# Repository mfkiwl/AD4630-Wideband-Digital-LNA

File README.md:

# AD4630 Wideband Digital LNA
## Introduction
Output noise is an important metric when it comes to evaluating the performance of precision voltage references (temperature coefficient and stability being others). Of particular interest is the frequency band between 0.1Hz and 10Hz. Most long-scale integrating ADCs feature measurement periods that lie in this band, so the internal reference should ideally have noise lower than measurement resolution over this time period. To measure noise in this band, an amplifier, itself having low noise, is needed. Appropriate filtering is also desired to keep out excess noise (of other frequencies) from contaminating the band of interest. 
## Project Motivation
This idea was originally proposed to me by [Marco Reps](https://www.youtube.com/@reps), which was in turn based on an idea [Mark](https://github.com/macaba) had told him about - a digital sampler that would send raw samples to a computer program that would filter to the required bandwidth digitally. Given the 2Msps sample rate of the AD4630, the upper frequency limit could be expanded to several kilohertz. The addition of a chopper preamp would also greatly reduce input noise. DC-coupling the input and adding a few preamps in parallel would also make a crude nanovoltmeter. This project is intended mainly to explore the AD4630 itself, and evaluate possible front end circuits.
### Goals:
- Wideband sampling and digitally filtering samples to desired bandwidth
- Ultralow 1/f corner front end with AC and DC paths for noise and nanovolt measurements (TBD)
- Optically isolated digital and analog sections: This is achieved easiest using a separate controller for front-end side, and using something like a UART isolator and a UART-USB bridge on the other side. 
- Battery powered (front end at least, digital section USB powered): This one might be a bit challenging, for example, what kind of batteries will be used? What voltages to power the front end with? Single ended or bipolar?
### Challenges: 
- Evaluating noise performance
- Implementing optical isolation and battery power
## Usage
### Specifications:
- 10mHz to 10kHz input bandwidth    [calculated]
- x200000 (106dB)                   [calculated]
- ~3.5nV/rtHz noise floor (full BW) [calculated]
## List of Files
- Hardware: KiCAD PCB files.

- Software: [under construction]
  - Simulation: LTspice .asc file.
- Resources: Infographics.
## Application Examples
[under construction]
- The LNA outputs raw samples that can be stored in a .csv file and interpreted by an [NSD](https://github.com/macaba/NSD) program. 
## Notes
- The AD4630 is pin-compatible with the AD4030, which opens up some interesting possibilities in the future.
- The input stage consists of a Sallen-Key filter that filters out frequencies below 10mHz while providing a gain of 330. It is possible to have gain and filtering in the same stage because of the low Thevenin resistance of the amplifier feedback resistors. The input filter/gain stage is followed by another x330 gain stage, which in turn is followed by a fully-differential amplifier (x2) to convert the input swing to a differential swing for the ADC. It should theoretically be possible to cancel reference noise by setting fully differential amplifier common mode voltage to 1/2\*Vref as well as referencing one of the ADC differential inputs to 1/2\*Vref. Overall gain is 200000.

## Links
- https://www.analog.com/media/en/technical-documentation/data-sheets/ad4630-24_ad4632-24.pdf
- https://www.analog.com/media/en/technical-documentation/data-sheets/ada4528-1_4528-2.pdf
- https://www.analog.com/media/en/technical-documentation/data-sheets/6362fa.pdf
- http://sim.okawa-denshi.jp/en/OPseikiHikeisan.htm
- http://www.dicks-website.eu/low_noise_amp_part1/part1.html

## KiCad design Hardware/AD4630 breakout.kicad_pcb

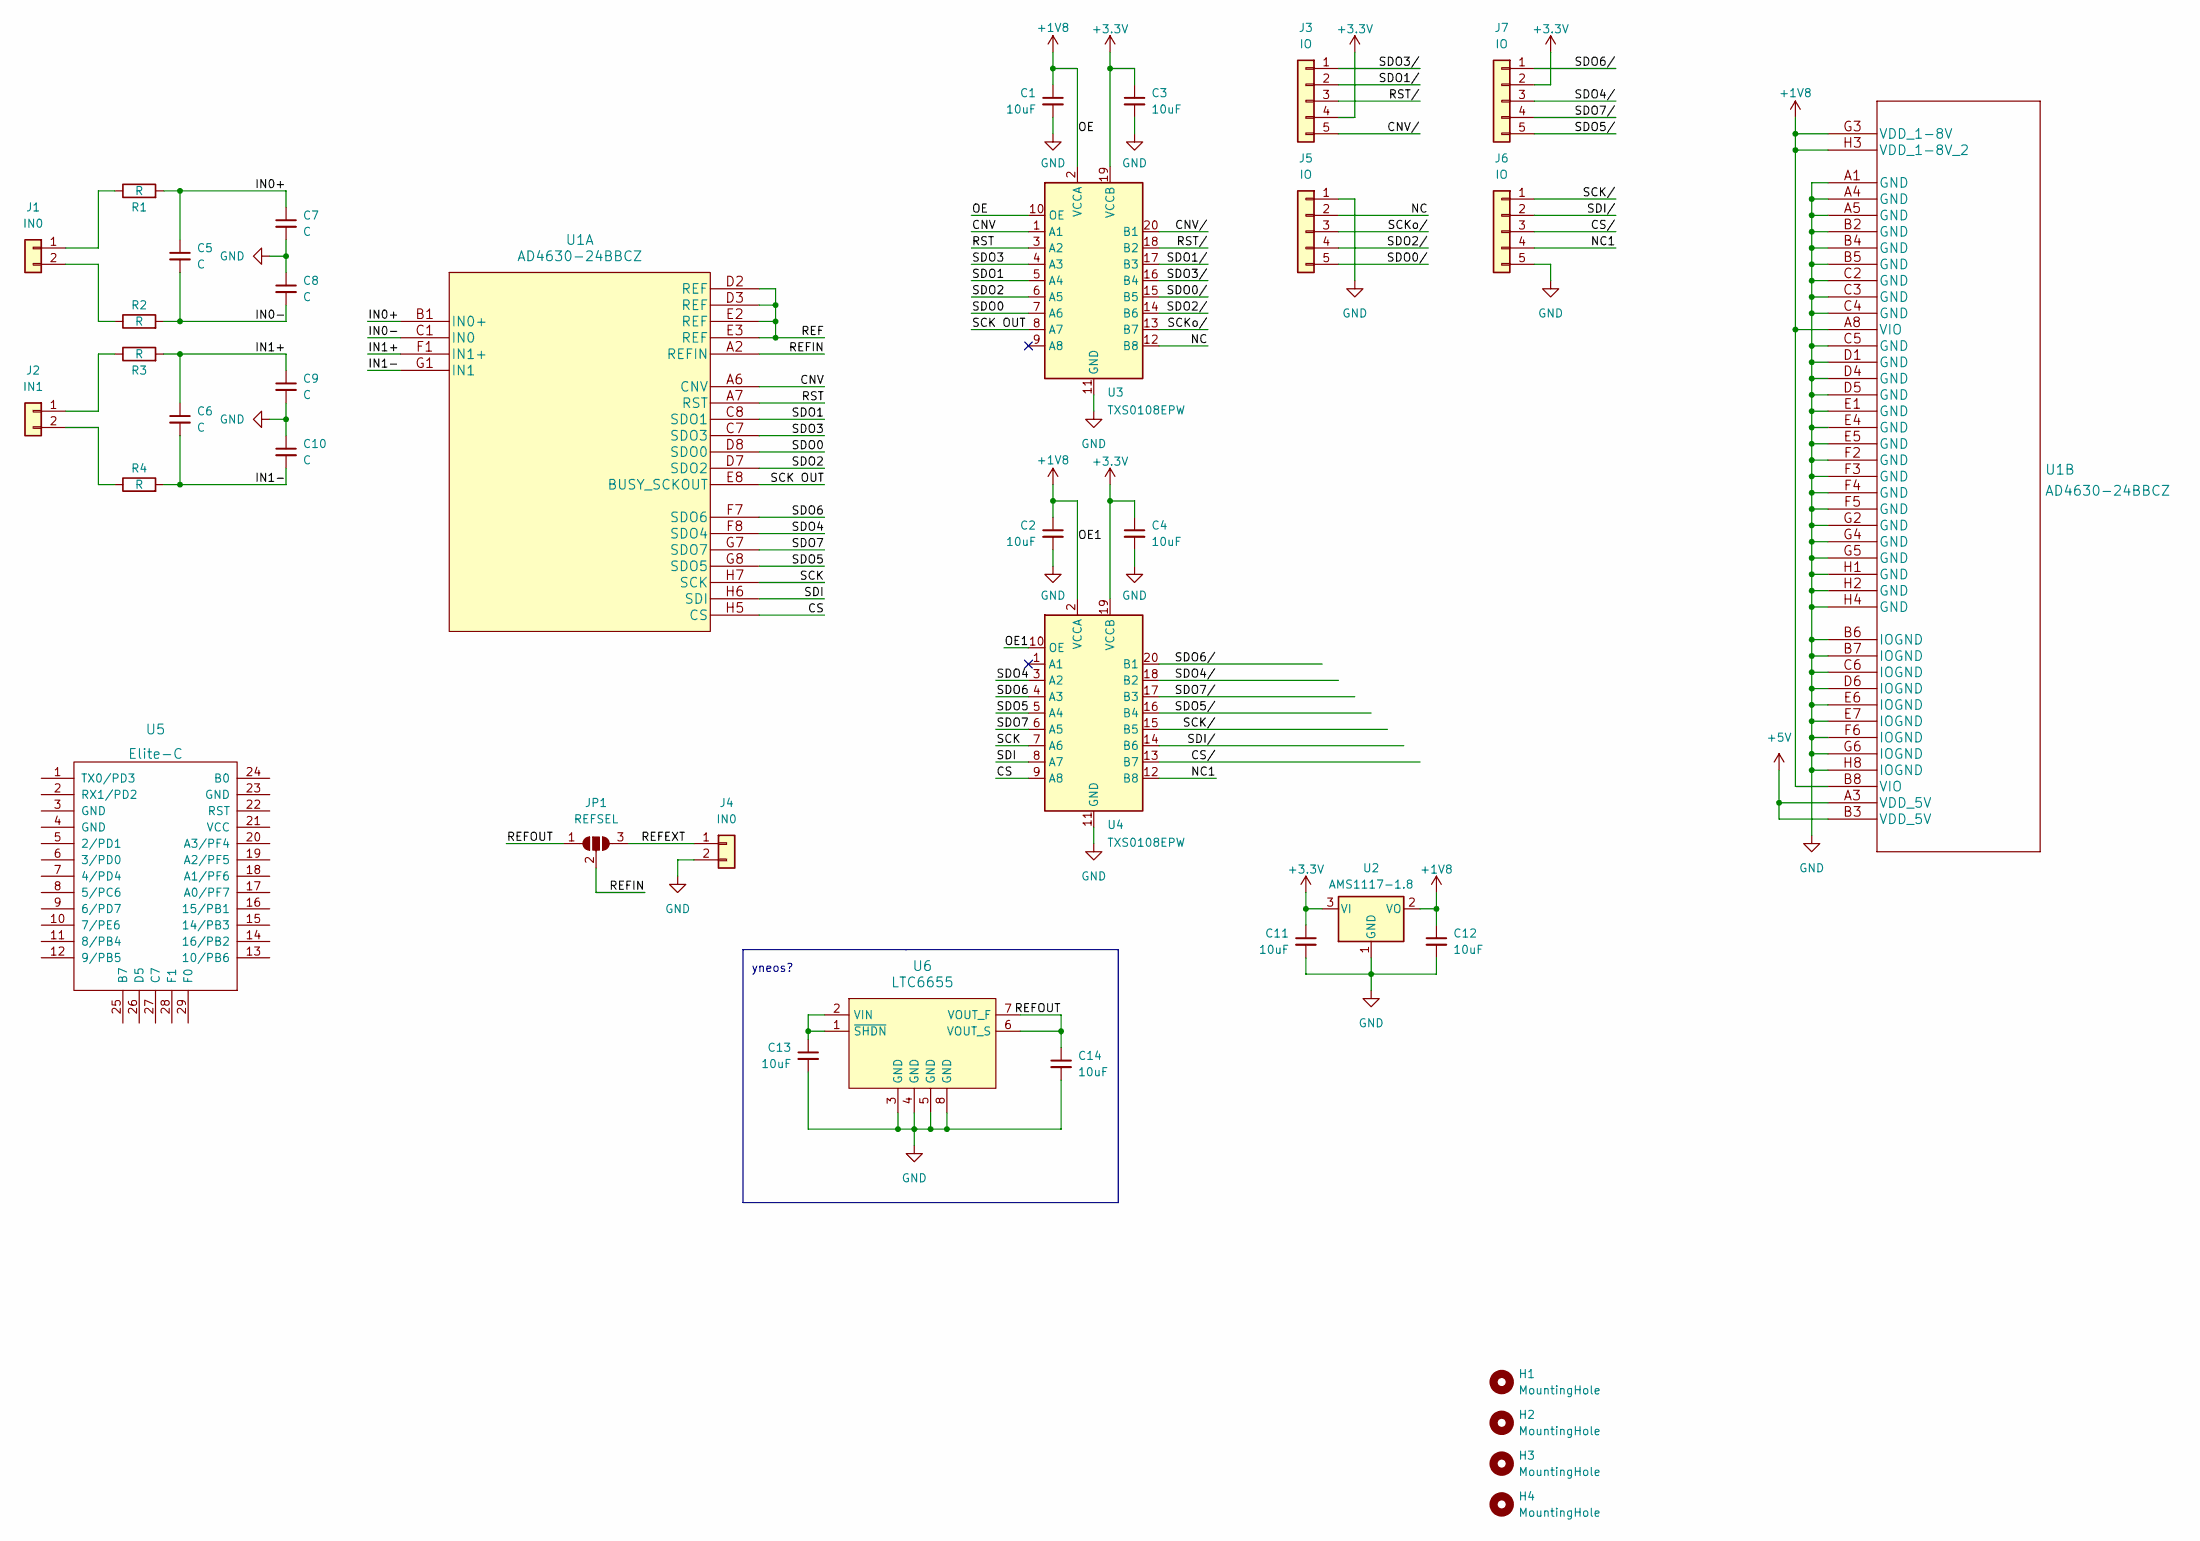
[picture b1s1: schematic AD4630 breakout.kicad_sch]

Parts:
C1, C2, C3, C4, C11, C12, C13, C14: 10uF; C_0603_1608Metric
C5, C6, C7, C8, C9, C10: C; C_0603_1608Metric
H1, H2, H3, H4: MountingHole; MountingHole_3.2mm_M3_Pad_Via
J1, J4: IN0; PinHeader_1x02_P2.00mm_Vertical
J2: IN1; PinHeader_1x02_P2.00mm_Vertical
J3, J5, J6, J7: IO; PinHeader_1x05_P2.00mm_Vertical
JP1: REFSEL; SolderJumper-3_P1.3mm_Open_RoundedPad1.0x1.5mm
R1, R2, R3, R4: R; R_0603_1608Metric
U1: AD4630-24BBCZ
U2: AMS1117-1.8; SOT-89-3
U3, U4: TXS0108EPW; TSSOP-20_4.4x6.5mm_P0.65mm
U5: Elite-C; Elite-C-castellated-29pin-holes
U6: LTC6655; LTC6655BHLS8-5-PBF

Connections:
+1V8: C1.1, C2.1, C12.1, U1.A8 (VIO), U1.B8 (VIO), U1.G3 (VDD_1-8V), U1.H3 (VDD_1-8V_2), U2.2 (VO), U3.2 (VCCA), U3.10 (OE), U4.2 (VCCA), U4.10 (OE)
+3V3: C3.1, C4.1, C11.1, J3.4, J7.2, U2.3 (VI), U3.19 (VCCB), U4.19 (VCCB)
+5V: U1.A3 (VDD_5V), U1.B3 (VDD_5V)
/CNV: U1.A6 (CNV), U3.1 (A1)
/CNV/: J3.5, U3.20 (B1)
/CS: U1.H5 (CS), U4.9 (A8)
/CS/: J6.3, U4.13 (B7)
/IN0+: C5.1, C7.1, R1.2, U1.B1 (IN0+)
/IN0-: C5.2, C8.2, R2.2, U1.C1 (IN0)
/IN1+: C6.1, C9.1, R3.2, U1.F1 (IN1+)
/IN1-: C6.2, C10.2, R4.2, U1.G1 (IN1)
/NC: J5.2, U3.12 (B8)
/NC1: J6.4, U4.12 (B8)
/REF: U1.D2 (REF), U1.D3 (REF), U1.E2 (REF), U1.E3 (REF)
/REFEXT: J4.1, JP1.3 (B)
/REFIN: JP1.2 (C), U1.A2 (REFIN)
/REFOUT: C14.1, JP1.1 (A), U6.6 (VOUT_S), U6.7 (VOUT_F)
/RST: U1.A7 (RST), U3.3 (A2)
/RST/: J3.3, U3.18 (B2)
/SCK: U1.H7 (SCK), U4.7 (A6)
/SCK OUT: U1.E8 (BUSY_SCKOUT), U3.8 (A7)
/SCKo/: J5.3, U3.13 (B7)
/SCK/: J6.1, U4.15 (B5)
/SDI: U1.H6 (SDI), U4.8 (A7)
/SDI/: J6.2, U4.14 (B6)
/SDO0: U1.D8 (SDO0), U3.7 (A6)
/SDO0/: J5.5, U3.15 (B5)
/SDO1: U1.C8 (SDO1), U3.5 (A4)
/SDO1/: J3.2, U3.17 (B3)
/SDO2: U1.D7 (SDO2), U3.6 (A5)
/SDO2/: J5.4, U3.14 (B6)
/SDO3: U1.C7 (SDO3), U3.4 (A3)
/SDO3/: J3.1, U3.16 (B4)
/SDO4: U1.F8 (SDO4), U4.3 (A2)
/SDO4/: J7.3, U4.18 (B2)
/SDO5: U1.G8 (SDO5), U4.5 (A4)
/SDO5/: J7.5, U4.16 (B4)
/SDO6: U1.F7 (SDO6), U4.4 (A3)
/SDO6/: J7.1, U4.20 (B1)
/SDO7: U1.G7 (SDO7), U4.6 (A5)
/SDO7/: J7.4, U4.17 (B3)
GND: C1.2, C2.2, C3.2, C4.2, C7.2, C8.1, C9.2, C10.1, C11.2, C12.2, C13.2, C14.2, J4.2, J5.1, J6.5, U1.A1 (GND), U1.A4 (GND), U1.A5 (GND), U1.B2 (GND), U1.B4 (GND), U1.B5 (GND), U1.B6 (IOGND), U1.B7 (IOGND), U1.C2 (GND), U1.C3 (GND), U1.C4 (GND), U1.C5 (GND), U1.C6 (IOGND), U1.D1 (GND), U1.D4 (GND), U1.D5 (GND), U1.D6 (IOGND), U1.E1 (GND), U1.E4 (GND), U1.E5 (GND), U1.E6 (IOGND), U1.E7 (IOGND), U1.F2 (GND), U1.F3 (GND), U1.F4 (GND), U1.F5 (GND), U1.F6 (IOGND), U1.G2 (GND), U1.G4 (GND), U1.G5 (GND), U1.G6 (IOGND), U1.H1 (GND), U1.H2 (GND), U1.H4 (GND), U1.H8 (IOGND), U2.1 (GND), U3.11 (GND), U4.11 (GND), U6.3 (GND), U6.4 (GND), U6.5 (GND), U6.8 (GND)
unnamed: C13.1, U6.1 (~SHDN), U6.2 (VIN)
unnamed: J1.1, R1.1
unnamed: J1.2, R2.1
unnamed: J2.1, R3.1
unnamed: J2.2, R4.1

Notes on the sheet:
yneos?

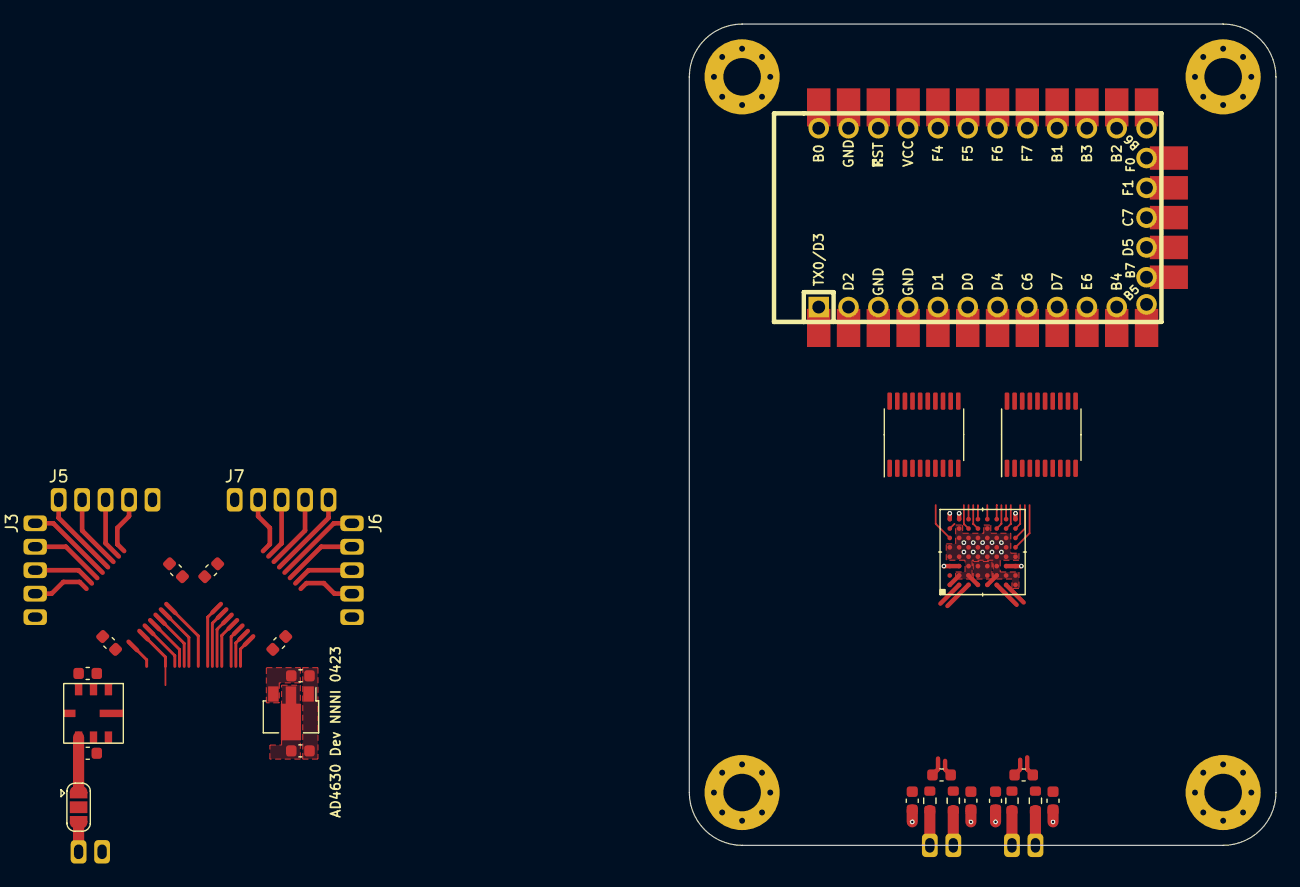
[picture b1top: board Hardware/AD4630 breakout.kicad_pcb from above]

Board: 4 copper layers, 50.0 x 70.0 mm, 36 parts (0 on the bottom side), 47 nets.

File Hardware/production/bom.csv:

Designator,Footprint,Quantity,Value,LCSC Part #
"C1, C11, C12, C13, C14, C2, C3, C4",C_0603_1608Metric,8,10uF,
"C10, C5, C6, C7, C8, C9",C_0603_1608Metric,6,C,
"J1, J4",PinHeader_1x02_P2.54mm_Vertical,2,IN0,
J2,PinHeader_1x02_P2.54mm_Vertical,1,IN1,
"J3, J5, J6, J7",PinHeader_1x05_P2.00mm_Vertical,4,IO,
"R1, R2, R3, R4",R_0603_1608Metric,4,R,
U1,AD4630-24BBCZ,1,AD4630-24BBCZ,
U2,SOT-89-3,1,AMS1117-1.8,
"U3, U4",TSSOP-20_4.4x6.5mm_P0.65mm,2,TXS0108EPW,
U6,LTC6655BHLS8-5-PBF,1,LTC6655,

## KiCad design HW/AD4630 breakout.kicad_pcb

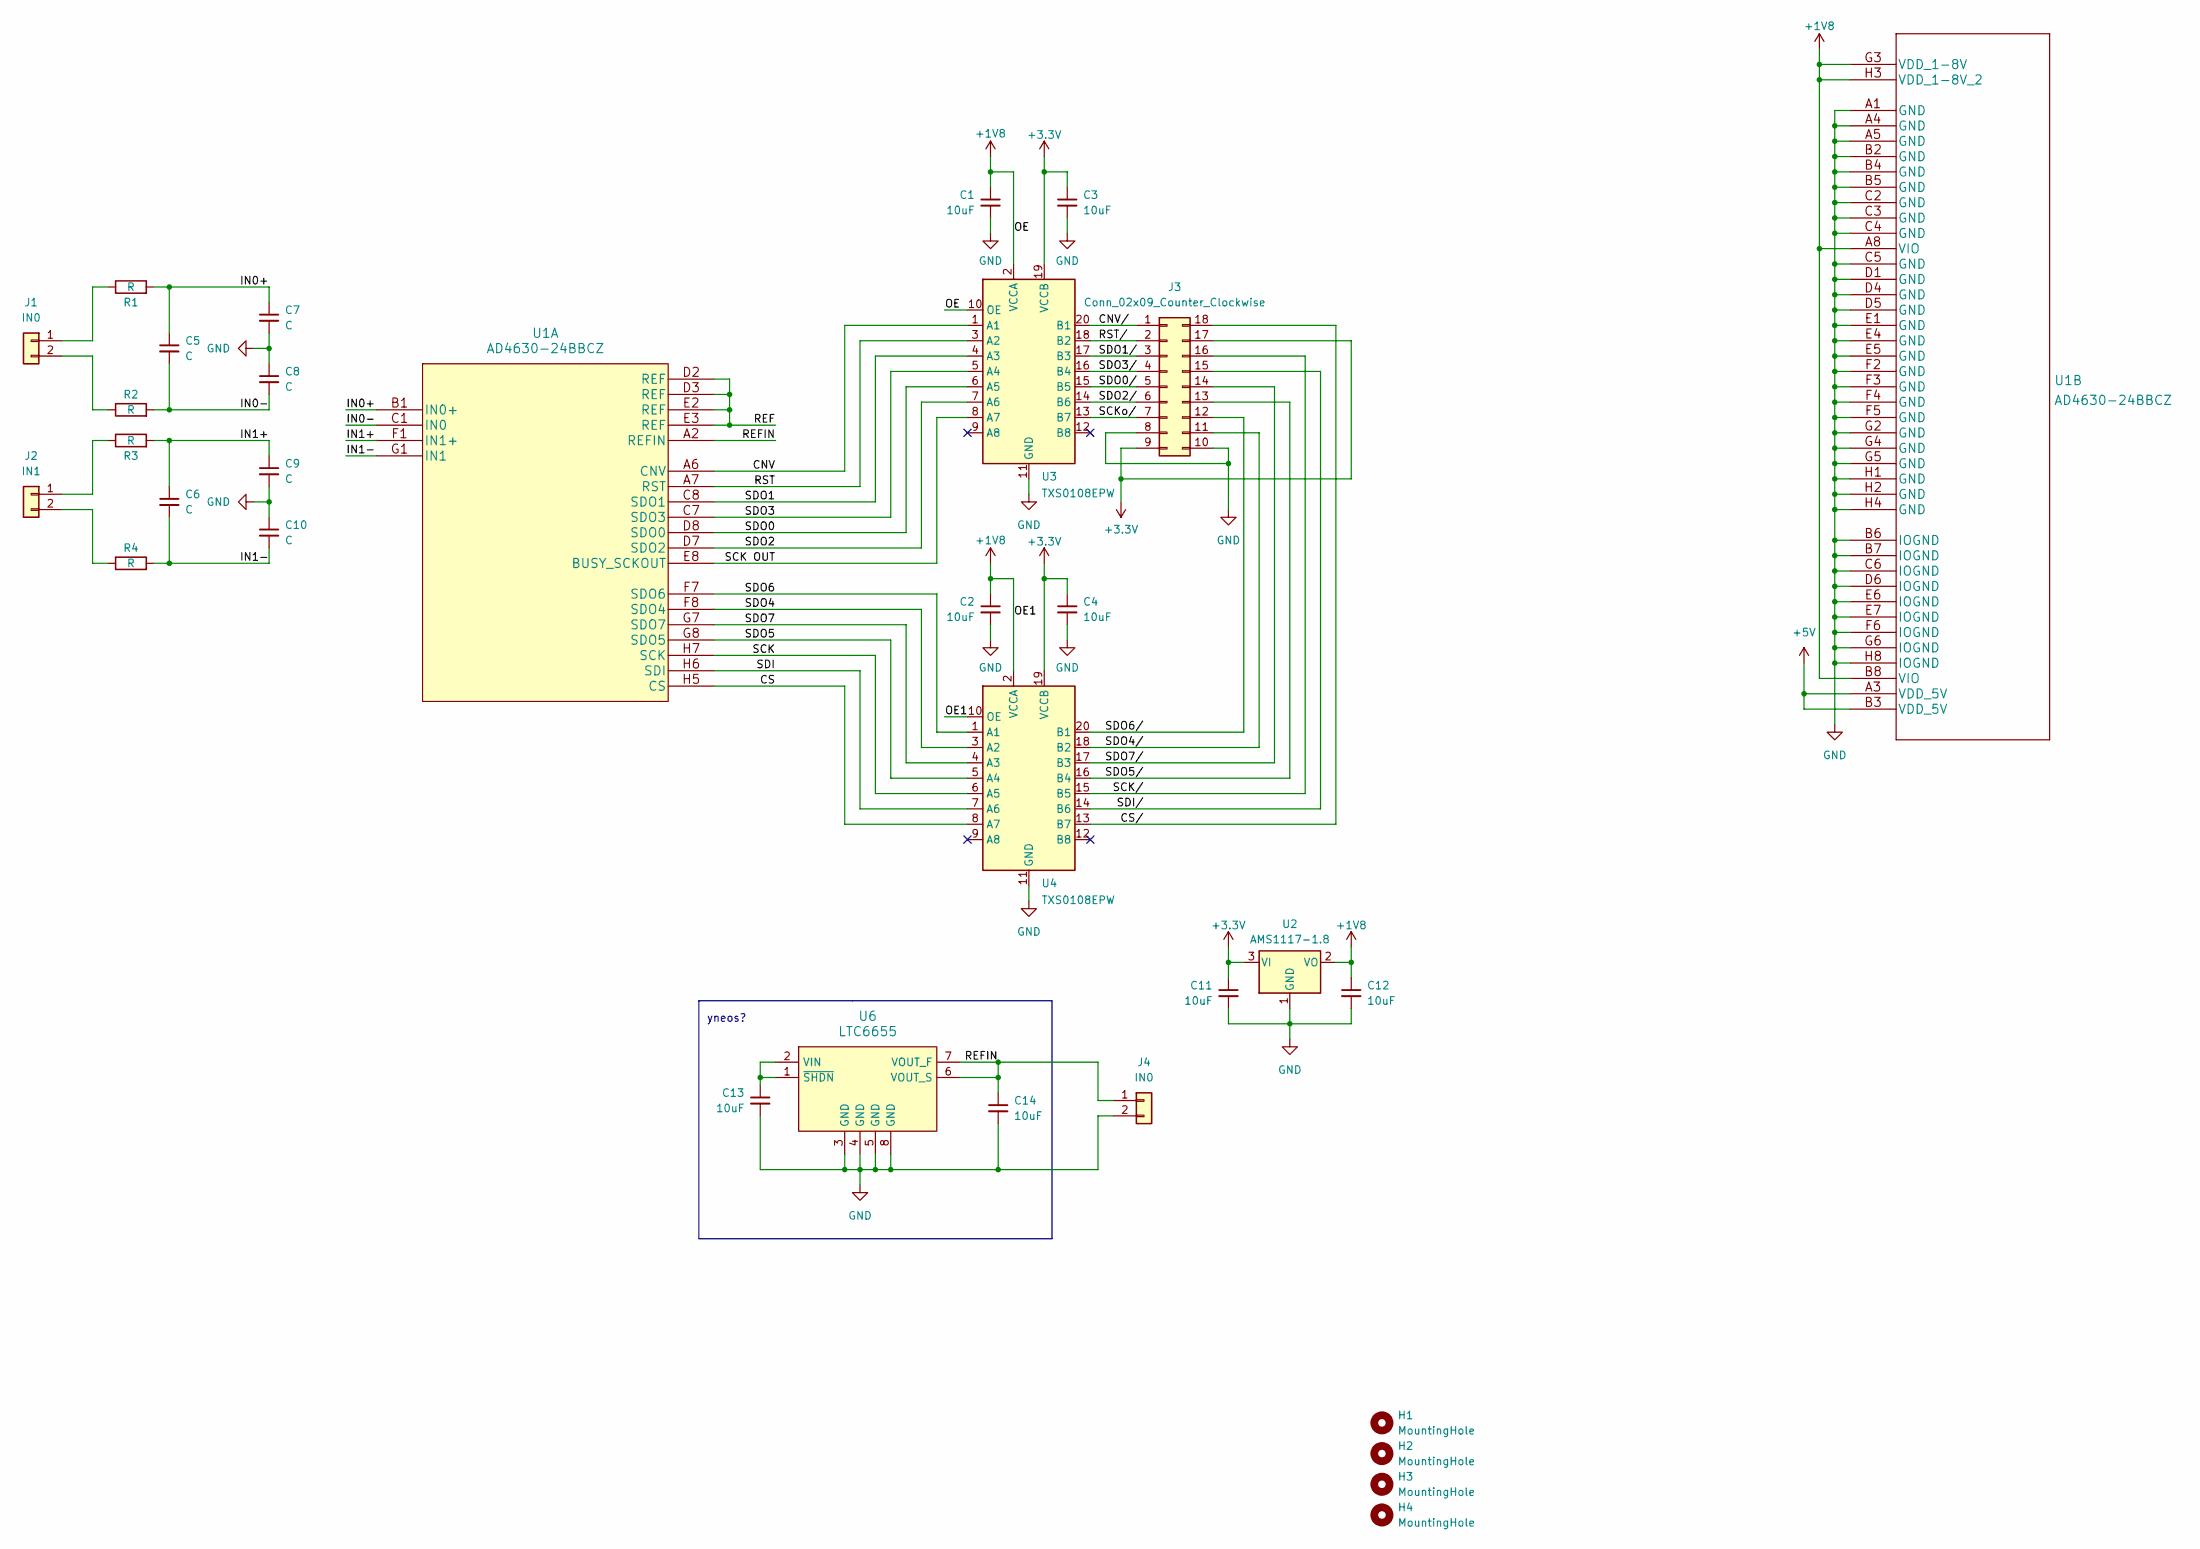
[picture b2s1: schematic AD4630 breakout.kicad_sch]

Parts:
C1, C2, C3, C4, C11, C12, C13, C14: 10uF; C_0603_1608Metric
C5, C6, C7, C8, C9, C10: C; C_0603_1608Metric
H1, H2, H3, H4: MountingHole; MountingHole_3.2mm_M3_Pad_Via
J1, J4: IN0; PinHeader_1x02_P2.54mm_Vertical
J2: IN1; PinHeader_1x02_P2.54mm_Vertical
J3: Conn_02x09_Counter_Clockwise; PinHeader_2x09_P2.54mm_Vertical
R1, R2, R3, R4: R; R_0603_1608Metric
U1: AD4630-24BBCZ
U2: AMS1117-1.8; SOT-89-3
U3, U4: TXS0108EPW; TSSOP-20_4.4x6.5mm_P0.65mm
U6: LTC6655; LTC6655BHLS8-5-PBF

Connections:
+1V8: C1.1, C2.1, C12.1, U1.A8 (VIO), U1.B8 (VIO), U1.G3 (VDD_1-8V), U1.H3 (VDD_1-8V_2), U2.2 (VO), U3.2 (VCCA), U3.10 (OE), U4.2 (VCCA), U4.10 (OE)
+3V3: C3.1, C4.1, C11.1, J3.9, J3.17, U2.3 (VI), U3.19 (VCCB), U4.19 (VCCB)
+5V: U1.A3 (VDD_5V), U1.B3 (VDD_5V)
/CNV: U1.A6 (CNV), U3.1 (A1)
/CNV/: J3.1, U3.20 (B1)
/CS: U1.H5 (CS), U4.8 (A7)
/CS/: J3.18, U4.13 (B7)
/IN0+: C5.1, C7.1, R1.2, U1.B1 (IN0+)
/IN0-: C5.2, C8.2, R2.2, U1.C1 (IN0)
/IN1+: C6.1, C9.1, R3.2, U1.F1 (IN1+)
/IN1-: C6.2, C10.2, R4.2, U1.G1 (IN1)
/REF: U1.D2 (REF), U1.D3 (REF), U1.E2 (REF), U1.E3 (REF)
/REFIN: C14.1, J4.1, U1.A2 (REFIN), U6.6 (VOUT_S), U6.7 (VOUT_F)
/RST: U1.A7 (RST), U3.3 (A2)
/RST/: J3.2, U3.18 (B2)
/SCK: U1.H7 (SCK), U4.6 (A5)
/SCK OUT: U1.E8 (BUSY_SCKOUT), U3.8 (A7)
/SCKo/: J3.7, U3.13 (B7)
/SCK/: J3.16, U4.15 (B5)
/SDI: U1.H6 (SDI), U4.7 (A6)
/SDI/: J3.15, U4.14 (B6)
/SDO0: U1.D8 (SDO0), U3.6 (A5)
/SDO0/: J3.5, U3.15 (B5)
/SDO1: U1.C8 (SDO1), U3.4 (A3)
/SDO1/: J3.3, U3.17 (B3)
/SDO2: U1.D7 (SDO2), U3.7 (A6)
/SDO2/: J3.6, U3.14 (B6)
/SDO3: U1.C7 (SDO3), U3.5 (A4)
/SDO3/: J3.4, U3.16 (B4)
/SDO4: U1.F8 (SDO4), U4.3 (A2)
/SDO4/: J3.11, U4.18 (B2)
/SDO5: U1.G8 (SDO5), U4.5 (A4)
/SDO5/: J3.13, U4.16 (B4)
/SDO6: U1.F7 (SDO6), U4.1 (A1)
/SDO6/: J3.12, U4.20 (B1)
/SDO7: U1.G7 (SDO7), U4.4 (A3)
/SDO7/: J3.14, U4.17 (B3)
GND: C1.2, C2.2, C3.2, C4.2, C7.2, C8.1, C9.2, C10.1, C11.2, C12.2, C13.2, C14.2, J3.8, J3.10, J4.2, U1.A1 (GND), U1.A4 (GND), U1.A5 (GND), U1.B2 (GND), U1.B4 (GND), U1.B5 (GND), U1.B6 (IOGND), U1.B7 (IOGND), U1.C2 (GND), U1.C3 (GND), U1.C4 (GND), U1.C5 (GND), U1.C6 (IOGND), U1.D1 (GND), U1.D4 (GND), U1.D5 (GND), U1.D6 (IOGND), U1.E1 (GND), U1.E4 (GND), U1.E5 (GND), U1.E6 (IOGND), U1.E7 (IOGND), U1.F2 (GND), U1.F3 (GND), U1.F4 (GND), U1.F5 (GND), U1.F6 (IOGND), U1.G2 (GND), U1.G4 (GND), U1.G5 (GND), U1.G6 (IOGND), U1.H1 (GND), U1.H2 (GND), U1.H4 (GND), U1.H8 (IOGND), U2.1 (GND), U3.11 (GND), U4.11 (GND), U6.3 (GND), U6.4 (GND), U6.5 (GND), U6.8 (GND)
unnamed: C13.1, U6.1 (~SHDN), U6.2 (VIN)
unnamed: J1.1, R1.1
unnamed: J1.2, R2.1
unnamed: J2.1, R3.1
unnamed: J2.2, R4.1

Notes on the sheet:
yneos?

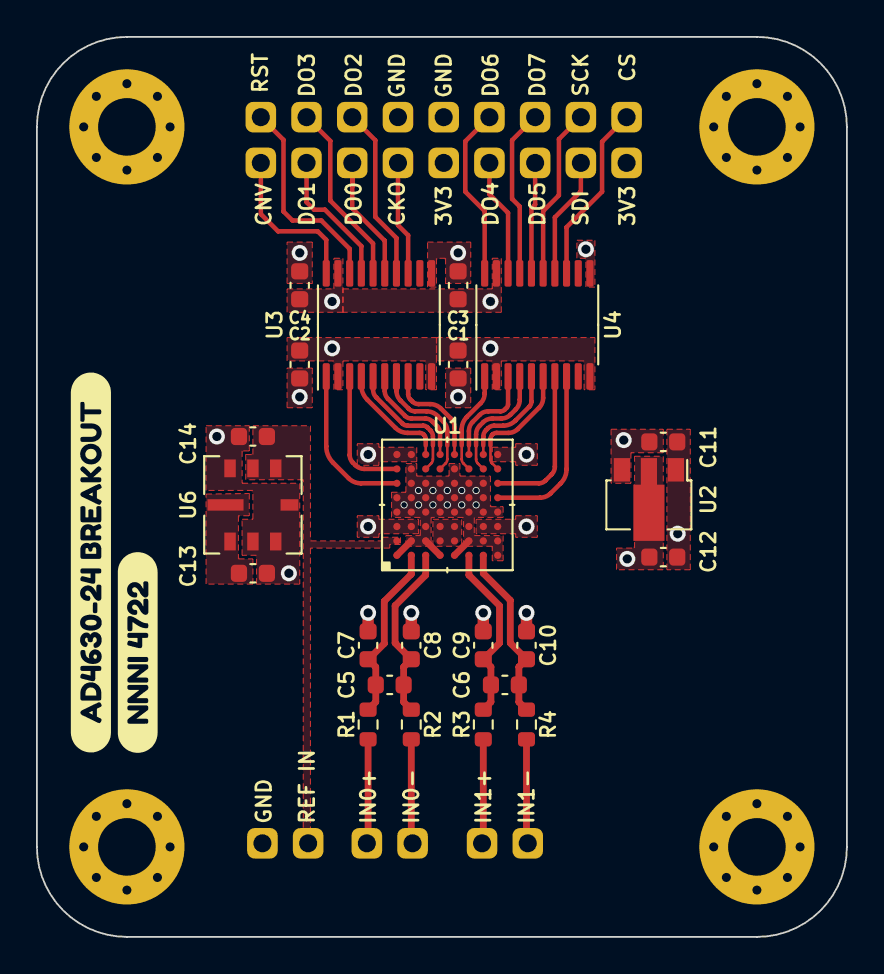
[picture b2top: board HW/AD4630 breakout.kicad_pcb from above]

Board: 4 copper layers, 45.0 x 50.0 mm, 33 parts (0 on the bottom side), 43 nets.

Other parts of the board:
kibuzzard-638251C8: G***; kibuzzard-638251C8
kibuzzard-638251EC: G***; kibuzzard-638251EC

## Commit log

2022-11-07 Project goals
2022-11-07 Added PCB Files
2022-11-07 Updated PCB
2022-11-12 added simulation file
2022-11-18 PCB updated
2022-11-26 Finished PCB
2022-11-29 Updated resources
2023-01-08 updated files
2023-01-10 added files
2023-01-16 sim chg
2023-01-23 added infographic
2023-01-23 updated simulation files

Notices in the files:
parts and their libraries:
Copyright 2021 Accelerated Designs. All rights reserved.
